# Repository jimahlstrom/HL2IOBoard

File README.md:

# IO Board for the Hermes Lite 2 by N2ADR
**January 6, 2024**

**Please click the left button "-  ----" above for a navigation menu.**

**Register names are now fixed, but there may be additions. Further documentation is coming, stay tuned.
Please provide feedback, especially if you see a problem.**

This project is a 5 by 10 cm printed circuit board and related firmware. The board mounts in the same box as the Hermes Lite 2.
It mounts above the N2ADR filter board if one is installed.
The filter board and the IO board are independent of each other.
The PC running the SDR software sends the transmit frequency to the board.
The microcontroller on the board then uses the board's switches to control an amplifier, switch antenns or transverters, etc.
There are a variety of IO resources available and there will be different microcontroller software for each application.
The IO board is meant to be a general purpose solution to control hardware attached to the HL2.

The IO board could also be connected to the I2C bus on a single board computer to provide station control.

The board has a Pico microcontroller and IO resources including
5 volt gates, low side switches, a fan controller, and a UART. There are two SMA connectors for a separate Rx input and a Pure Signal input.
The board plugs into the [Hermes Lite 2](http://www.hermeslite.com) main board and replaces the 2x20
jumper that connects to the N2ADR filter board.
The board sits directly above the filter board (if any) as shown in the photos below.

To use the board it will be necessary to choose which switches you need and solder wire jumpers from the switches to the DB9 connector.
Then you must write or download firmware for the Pico that will operate the switches based on the transmit frequency.

#### IO board mounted above the filter board

#### Top view of the board

#### Bottom view of the board

## Modification to the HL2 Main Board
The HL2 main board must be modified by adding three extra header pins. In the picture below, look at the normal 20 pin
header at the back edge of the board. Following that, two holes are skipped, and then a 1x3 header is added. This changes the
20 pin header to a 25 pin header with two unused pins. The extra pins provide 3.3 volts, ground and VSUP.
VSUP is the 12 volt HL2 input supply taken after the fuse.
It is convenient to place the 2x20 pin header across the existing pins and the three added pins to provide
alignment when soldering. The IO board has a 2x25 pin header. When installed, this connects the HL2 to the filter board as usual.

For the three-pin header you need the same size as the 1x20 header on the main HL2 board. The pin pitch is 2.54 mm.
On my HL2, the total height is 11.43 mm with 3.05 mm below the PCB. The pins are square and 0.64 mm on a side.
But my HL2 is an old one, so check what size your pins are. The exact height is not too critical.

#### Added three-pin header

## Initial Testing of the IO Board
Please test the IO board when you get it.
First program the Pico with the test program.
Power off the HL2 and connect a USB cable to the IO Board.
Push the button on the Pico and then plug the USB cable into your PC.
The Pico will appear as a flash drive on the PC. Then copy the file n2adr_test/build/main.uf2 to the Pico. The Pico will reboot and the Pico LED will flash slowly.

Now apply power to the HL2. Use an oscilloscope to see the test signals.
  * Look for pulses of 1,2,3,4,5,6,7 milliseconds on J4 pins 1 to 7.
  * Look for 3.0 volts DC on J4 pin 8.
  * Look for 0.5 * supply voltage at J3 pin 1.
  * Look for a 5.0 volt 500 Hz square wave at Sw5.
  * Look for a supply voltage 250 Hz square wave at Sw12.

Connector J6 has MOSFETs that short the pin to ground.
To test, connect a DC voltage of 3.3 to 16 volts to one end of a resister of a few thousand ohms.
Connect the other end to an oscilloscpe, and use this end to probe J6 pins 1 to 7.
You should see the same signal as on J4 but with reverse polarity.

The test program can generate a test pattern for the antenna tuner protocol. Write a "1" to REG_ANTENNA_TUNER. SDR authors can use this to help write code for this feature. 

## Design of the IO Board Hardware
The IO board is a four-layer PCB. Rather large parts are used, with none smaller than 0805 (2012 metric). It is designed to be easy to solder at home. It is only necessary to mount the parts you plan to use.

Please refer to the [schematic](KiCad/HL2IOBoard.pdf).
The IO board has two I2C addresses. Address 0x41 register 0 is a read only register that returns the hardware version number
in bits 3 to 0, and 0xF in bits 7 to 4. So for this hardware version, it returns 0xF1. If other IO boards become available,
they will return different version numbers. This is the hardware version and will be returned even if the firmware is not running.
Reading this register can test whether the filter board is installed.

The Pico microcontroller listens to I2C address 0x1D. This is distinct from the filter board I2C address, and the IO board will
not conflict with or control the filter board. The IO board has these resources controlled by the Pico:

 * Eight 5 volt CMOS outputs and eight low-side switches (mosfets to ground). Both are controlled by the same Pico pin,
so they can be used in any combination, but only up to eight total. They are high speed except for output 8. This has an RC filter and is intended for
optional zero to five volt PWM DC output. The DC output can be programmed to change according to the band in use, and is used to
change bands in external amplifiers. If not needed, output 8 can still be an output, but at slow speed.
 * Five logic inputs that are protected, and work from plus 3.3 to 20 volts.
 * A source of switched 12 volt power.
 * A source of switched 5 volt power.
 * A variable DC voltage from zero to about 12 volts. This is intended to drive a fan.
 * A logic input that reads the state of EXTTR from the HL2.
 * An SMA receive input.
 * Control for a switched high pass filter in the receive input.
 * An SMA Pure Signal input.
 * Pico GPIO 5 is unused.
 * Pico GPIO 26, 27 and 28 are unused. They can be used for 3.3 volt logic or for ADC inputs. The ADC reference is 3.00 volts.
 * Any Pico pins can be used directly at 3.3 volt logic.

These resources can be used for various purposes. The Pico has two UARTs. Output 1 and Input 1 can be used for UART Tx and Rx.
Note that the signal voltages are zero and five volts. This is common for communication between microcontrollers.
But the standard RS232 levels are more like plus and minus eight volts, so a connection to a PC will require an interface IC.

A "low-side switch" is a mosfet to ground. They are commonly used to switch relays. But they can also implement a wired-or bus
such as a one-wire bus or an I2C bus. The Icom AH-4 antenna tuner can be controlled this way. The switches are implemented
in a TBD62381AFWG,EL integrated circuit. This has an absolute maximum rating of 50 volts and 500 ma per channel.

**These low-side switches are NOT protected against inductive loads. Always place a diode across relay coils and any other inductive load.**

There is a 15x18 mm bare copper area for prototyping. There is a 1x5 header J2 and a 1x2 header J12 to plug in a perf board for additional area.

The board has a DB9 connector and the pins are wired to a 1x9 pin header. The outputs go to two 2x4 headers, and the inputs go to a 1x5 header.
Other IO goes to small pads. The headers are not installed. Wire everything up as desired with hookup
wire to the pads and to the DB9 pads. Of course, you can add headers if desired.

### Table of IO Resources

|Software Pin Name |Usage|Connector Reference|
|------------------|-----|-------------------|
|GPIO00_HPF|Control HPF in Rx path||
|GPIO01_Sw12|Switched VSUP (usually 12 volts)|Sw12|
|GPIO02_RF3|Control Pure Signal input||
|GPIO03_INTTR|Control HL2 T/R relay||
|GPIO04_Fan|Zero to 11.5 fan voltage|J3|
|GPIO05_xxx|not connected||
|GPIO06_In5|Protected logic input|J8 pin 5|
|GPIO07_In4|Protected logic input|J8 pin 4|
|GPIO08_Out8|5V logic ; low side switch|J4 pin 8 ; J6 pin 8|
|GPIO09_Out7|5V logic ; low side switch|J4 pin 7 ; J6 pin 7|
|GPIO10_Out5|5V logic ; low side switch|J4 pin 5 ; J6 pin 5|
|GPIO11_Out4|5V logic ; low side switch|J4 pin 4 ; J6 pin 4|
|GPIO12_Sw5|Switched 5 volts|Sw5|
|GPIO13_EXTTR|Logic input EXTTR, High for Rx, low for Tx||
|GPIO14_I2C1_SDA|HL2 I2C bus||
|GPIO15_I2C1_SCL|HL2 I2C bus||
|GPIO16_Out1|5V logic ; low side switch|J4 pin 1 ; J6 pin 1|
|GPIO17_In1|Protected logic input|J8 pin 1|
|GPIO18_In2|Protected logic input|J8 pin 2|
|GPIO19_Out2|5V logic ; low side switch|J4 pin 2 ; J6 pin 2|
|GPIO20_Out3|5V logic ; low side switch|J4 pin 3 ; J6 pin 3|
|GPIO21_In3|Protected logic input|J8 pin 3|
|GPIO22_Out6|5V logic ; low side switch|J4 pin 6 ; J6 pin 6|
|GPIO25_LED|Pico on-board LED||
|GPIO26_ADC0|not connected||
|GPIO27_ADC1|not connected||
|GPIO28_ADC2|not connected||

## IO Board Pico Firmware
### Installing Firmware
Firmwares for the Pico are in subdirectories of HL2IOBoard. Look in the source files to see what they do.

- n2adr_test   Test program to toggle the 5 volt outputs.
- n2adr_basic  Very basic example.
- n2adr_lib    Library of useful subroutines used in the above.
- n1adj_hr50   Control the [Hardrock-50](https://hobbypcb.com/products/hardrock-50-hf-power-amp-kit) amplifier.

To create your own firmware, install the Pico SDK and create a directory for your code.
You may want to clone my github project to get you started.
Export the location of your SDK: export PICO_SDK_PATH=/home/jim/etc/pico-sdk.
Copy the file pico-sdk/external/pico_sdk_import.cmake to your directory.
Copy my CMakeLists.txt and main.c to your directory and edit them as desired.
Make a "build" subdirectory.
Change directories to the build directory and enter "cmake .." and "make".
See the Pico documentation for more detail.
Be careful with i2c_slave_handler(), as it is an interrupt service routine. Return quickly and do not put printf's here! Just set a flag and look for it in the loop at the end of main().

To install the firmware, power off the HL2 and connect a USB cable to the IO Board.
Push the button on the Pico and then plug the USB cable into your PC.
The Pico will appear as a flash drive on the PC. Then copy the file build/main.uf2 to the Pico. 

There is an LED on the Pico. When the firmware is running, it flashes slowly. When the Pico receives I2C traffic directed to its address, it flashes faster.

### Firmware Design

The Pico listens to I2C address 0x1D and you can read and write to registers at this I2C address. Writes always send a one-byte address and one byte of data. Since the address is one byte, the data item is stored in a 256 byte array named "Registers".
All registers are initialized to zero at power on and after a software reset.
You can write to any register, not just the ones in the table below.
So a write to register REG_ANTENNA_TUNER (equal to 7) looks like this:

Registers[REG_ANTENNA_TUNER] = datum;

Reads always send a one byte address and return four bytes of data.
A read from register REG_ANTENNA_TUNER returns Registers[REG_ANTENNA_TUNER] and the next three registers.

There are some exceptions to this general pattern and all are noted below.

The Pico is an I2C slave device, so reads and writes result in a call to the interrupt service routine
in i2c_slave_handler.c. This routine must return fast to avoid hanging the bus. So a typical program would
not alter i2c_slave_handler.c. It would have a polling loop in main.c to check for changes in any registers
it cares about and would perform needed actions there.

#### Frequency Codes

The files n2adr_lib/frequency_code.c and frequency_code.py contain functions to convert a frequency in hertz to a one-byte code,
and to convert a code back to a frequency. The code is a useful one-byte approximation of the frequency
which is sufficient to recognize the band and to select antennas.
The codes are monotonic in frequency. The special code zero means the frequency was not entered and is unspecified.
A table of all the codes is at [frequencycodes.html](http://james.ahlstrom.name/frequencycodes.html).
Run the Python file "python frequency_code.py" to print your own table of codes.

#### Band Codes

A band code is a single frequency code for each band.
The band code is chosen to be as close to the band frequency as possible. All other frequency codes are assigned to the closest band code.
A table of band codes is in hl2ioboard.h.
You can use the band code to select antennas, or you can use the frequency code directly.

The band code is convenient because some bands have multiple frequency codes. And since all frequency codes resolve to the
closest band code, there are no gaps in coverage. If you tune outside the band, the closest band antenna is chosen.

#### Global Variables

These global variables are set in i2c_slave_handler() when data is received:

  * extern uint64_t new_tx_freq;
  * extern uint8_t new_tx_fcode;

The Tx frequency and Tx frequency code are set when the Tx frequency changes.

  * extern bool rx_freq_changed;
  * extern uint8_t rx_freq_high;
  * extern uint8_t rx_freq_low;

These are set when any of the twelve Rx frequencies change. If all Rx frequencies are zero, rx_freq_high and low are both zero.

  * extern uint8_t Registers[256];

This is the array of all register data.

  * extern uint8_t firmware_version_major;
  * extern uint8_t firmware_version_minor;

You must set the version in your main routine so it can be returned to software.

#### Library Functions

The directory n2adr_lib contains utility functions to make writing Pico software easier.

  * void configure_led_flasher(void)

Call this once near the start of your Pico program. It controls flashing the Pico LED.

  * void configure_pins(bool use_uart1, bool use_pwm4a)

This sets the configuration of the Pico GPIO pins, and you must call this once near the start of your program.
If use_uart1, J8 pin 1 and J4 pin 1 are UART pins; otherwise they are regular logic.
If use_pwm4a, J4 pin 8 is used for a variable 0 to 5 volt band voltage; otherwise it is regular logic.

  * uint8_t hertz2fcode(uint64_t hertz)
  * uint64_t fcode2hertz(uint8_t code)

These functions convert between a 5-byte frequency and a 1-byte frequency code. They are in frequencycode.c.
The file frequencycode.py is the same code in Python, and it is not used here. It is included for convenience.

  * uint8_t fcode2band(uint8_t fcode)

This converts a frequency code to a band code. A band code is a single frequency code for each band. See below.

  * void ft817_band_volts(uint8_t band_code)
  * void xiegu_band_volts(uint8_t band_code)

These are used to generate a zero to five volt band voltage on J4 pin 8.

  * i2c_slave_handler.c

This contains the I2C interrupt handler that is called for I2C reads and writes. Since it must return quickly,
it mostly sets registers and global variables that you can test in a loop in your Pico program.
When it receives the Tx frequency, it sets new_tx_freq to the frequency and new_tx_fcode to the corresponding frequency code.
It also uses firmware_version_major and firmware_version_minor, and you must set these in your Pico program.

  * icom_ah4.c

This contains code to control the Icom AH4 antenna tuner. It is untested.

#### Table of I2C Registers

When you write code, please use the register names shown. The names are in i2c_registers.h.

|Register|Name|Description|
|--------|----|-----------|
|0|REG_TX_FREQ_BYTE4|Most significant byte of the 5-byte Tx frequency in Hertz|
|1|REG_TX_FREQ_BYTE3|Next Tx frequency byte|
|2|REG_TX_FREQ_BYTE2|Next Tx frequency byte|
|3|REG_TX_FREQ_BYTE1|Next Tx frequency byte|
|4|REG_TX_FREQ_BYTE0|The least significant byte of the Tx frequency.|

The transmit frequency is a five-byte integer number in hertz. You can send BYTE1 to BYTE4 in any order.
When BYTE0 is sent, the Pico will update the global 64-bit integer new_tx_freq and the 8-bit frequency code new_tx_fcode.
This happens in an interrupt service routine in n2adr_lib/i2c_slave_handler.c.
Use a polling routine in your main.c to look for changes. See the example in n2adr_basic.
If a transverter is in use, the Tx frequency includes the transverter offset.

|Register|Name|Description|
|--------|----|-----------|
|5|REG_CONTROL|Write 1 to reset all the registers to zero.|
|6|REG_INPUT_PINS|Read only. The input pin bits: In5, In4, In3, In2, In1, Exttr|
|7|REG_ANTENNA_TUNER|Control an antenna tuner|

A write to register REG_ANTENNA_TUNER is a command to the tuner. I am modeling this on the Icom AH-4 but I want it to work in general.
See the code in n2adr_lib/icom_ah4.c.
A write of 1 starts a tune request.
A write of 2 is a bypass command. Other tuners may have more commands. The Pico will talk to the ATU and change the register to higher numbers to indicate progress.
The PC must read this register while tuning progresses. If the register reads as 0xEE the PC must send RF to the ATU, and stop RF when 0xEE stops.
A final value of zero indicates a successful tune. Values of 0xF0 and higher indicate that tuning failed.
Note that the IO board can not initiate RF and so the need for 0xEE.
SDR software is not required to implement this command. In the future there may be an external program to do this.

|Register|Name|Description|
|--------|----|-----------|
|8|REG_FAULT|Read only. Zero for no fault. The meaning of non-zero codes is not currently defined.|
|9|REG_FIRMWARE_MAJOR|Read only. Firmware major version|
|10|REG_FIRMWARE_MINOR|Read only. Firmware minor version|
|11|REG_RF_INPUTS|The receive input usage, 0, 1 or 2.|

REG_RF_INPUTS determines how the SMA receive input J9 and the Pure Signal input J10 are used.
Mode 0 means that J9 is not used, and the usual HL2 input is the receive input.
In mode 0 the Pure Signal input J10 is mixed with the receive signal.
For modes 1 and 2, J9 is used instead of the usual HL2 receive input.
Mode 1 means that J9 is used for the receive signal and the Pure Signal input is not available.
Mode 2 means that for receive, J9 is used for the receive signal;
and that for transmit, the Pure Signal input is passed to the HL2 instead of a receive signal.

|Register|Name|Description|
|--------|----|-----------|
|12|REG_FAN_SPEED|The fan voltage as a number from 0 to 255|
|13|REG_FCODE_RX1|The frequency code for the first receiver RX1|
|14-24|REG_FCODE_RX2 to RX12|The frequency code for receiver RX2 to RX12|

The HL2 can have from one to twelve independent receivers. SDR software can use this feature
to scan multiple bands for digital or CW signals. Choosing an antenna requires knowing all the Rx frequencies.
The Rx frequencies are sent as a one-byte frequency code to registers 13 to 24 with names REG_FCODE_RX1 to RX12.
The HL2 always has RX1, but if it is unspecified (zero) it is the same as the Tx frequency.
If any Rx frequency is changed, the global boolean rx_freq_changed is set to true.
If a transverter is in use, the Rx frequency includes the transverter offset.

|Register|Name|Description|
|--------|----|-----------|
|25|REG_ADC0_MSB|The most significant byte of ADC0|
|26|REG_ADC0_LSB|The least significant byte of ADC0|
|27|REG_ADC1_MSB|The most significant byte of ADC1|
|28|REG_ADC1_LSB|The least significant byte of ADC1|
|29|REG_ADC2_MSB|The most significant byte of ADC2|
|30|REG_ADC2_LSB|The least significant byte of ADC2|

The Pico has one 12-bit ADC that can read from ADC0, ADC1 and ADC2 on pins GPIO26, GPIO27 and GPIO28.
Always read the most significant byte first because that triggers the conversion.
A read from ADC0 returns the value of ADC0 and ADC1 in the four byte response.
A read from ADC1 returns the value of ADC1 and ADC2.
Reading the two values in quick succession can be used to calculate SWR from forward and reverse power.

|Register|Name|Description|
|--------|----|-----------|
|31|REG_ANTENNA|Choose among multiple antennas|

Normally, the antenna choice is calculated by the Pico based on the Tx and Rx frequencies.
But there may be multiple antennas available for a single band.
The high four bits of REG_ANTENNA is the Tx antenna, and the low four bits is the Rx antenna for the current band.
A zero means the first (default) antenna.

|Register|Name|Description|
|--------|----|-----------|
|32|REG_OP_MODE|Set the operating Mode|

||Mode|Value|Mode|Value|Mode|Value|Mode|Value|
|---|---|---|---|---|---|---|---|---|
||LSB|0|USB|1|DSB|2|CWL|3|
||CWU|4|FM|5|AM|6|DIGU|7|
||SPEC|8|DIGL|9|SAM|10|DRM|11|
||AM_LSB|12|AM_USB|13|

Operating mode values are based on Thetis internal definitions.
Note that value zero does not mean "unspecified".

|Register|Name|Description|
|--------|----|-----------|
|167|REG_STATUS|Read or write to Sw5 and Sw12. Read the In1 configuration.|
|168|REG_IN_PINS|Same as REG_INPUT_PINS plus Out1 and Out8 configuration.|
|169|REG_OUT_PINS|Read or write to GPIO Out8 to Out1 directly.|
|170|GPIO_DIRECT_BASE|Map this register to GPIO 0|
|171-198||GPIO 1 to 28|

A read or write to registers GPIO_DIRECT_BASE to GPIO_DIRECT_BASE + 28 reads or writes to the Pico GPIO pins 0 to 28.
This supports using Steve's hermeslite.py or similar to control the Pico registers directly.
A user could write a program to switch antennas without adding C code to the Pico.
Since the SDR program writes Tx and Rx frequencies to the Pico, a third party program could read them back to select the antenna.
For C programmers, it would still be easier to write the code into the Pico.

The other registers add further support. Bits are numbered from 7 to zero and the most significant bit is 7.

  * REG_STATUS

Bit 0 is Sw5, bit 1 is Sw12, bit 2 is 1 if In1 is configured as a UART.

  * REG_IN_PINS

This is read-only. It is the same as REG_INPUT_PINS, and adds two bits. Bit 6 is 1 if Out1 is configured as UART.
Bit 7 is 1 if Out8 is configured as band volts.

  * REG_OUT_PINS

This reads and writes Out1 to Out8 directly. Bit 0 is Out1 and bit 7 is Out8.

|Register|Name|Description|
|--------|----|-----------|
|200-255||Reserved for SDR authors. If you use them, please document them.|

## Modifications to SDR PC Software

The IO board connects to the I2C interface in the Hermes Lite 2.
The [HL2 protocol](https://github.com/softerhardware/Hermes-Lite2/wiki/Protocol)
provides a way to send and receive I2C messages from host SDR software to the IO board to control its operation.
Quisk uses the ACK bit with I2C commands. As described in the protocol, these commands should
be sent at intervals so they don't disrupt normal protocol commands.

Since the PC can read and write the I2C bus to communicate with the IO board, it would be possible for SDR software
authors (Quisk, Spark, Power SDR, etc.) to write extensive logic to control IO. This is NOT the desired result. Instead
users should write new Pico firmware to provide the services they require. It is easy to write firmware for the Pico.
Ideally, an owner of a given power amp, for example HR50, would write a custom firmware and provide a wiring diagram for that amp.

**Do NOT ask authors to modify SDR software! Write new firmware instead!**

### Reset

The IO board registers are static and may have old data.
When your SDR program starts, write 1 to REG_CONTROL to set all registers back to zero.

### Transmit Frequency

The only required SDR modification is sending the transmit frequency.
SDR software must send the transmit frequency to provide band information to power amps, transverters and loop antennas.
You can wait for the band to change, and then just send a frequency in the band. For example, if the
user presses the 40 meter button, send 7.0 MHz. This is enough to determine the band, but not enough to tune a loop antenna.
You can send the exact Tx frequency, but since the user is probably doing a lot of tuning, it is best to limit the I2C
traffic. Quisk sends the Tx frequency at a maximum rate of once every 0.5 seconds, and only if it changes. The frequency
data in registers BYTE1 to BYTE4 are static, and are only used when register BYTE0 is written. So you don't need to re-send them unless
they change.

### Receive Frequencies

You may need to send the twelve receive frequencies if your SDR software supports multiple receivers.
The Pico will use this to select a receive antenna, probably by finding the highest frequency and
setting low pass filters to that band. If all Rx frequencies are zero, the Rx band is the same as Tx.

### RF Receive Input

The mode control REG_RF_INPUTS is 0, 1 or 2, and is a user setting. There needs to be an option to set this.

### Fan Control

The fan speed control can be an internal calculation based on temperature, as is currently the case for the fan control
in the HL2 gateware. I don't see the need for a user option for this. Quisk does not implement the fan.

## IO Board Control Software

The software directory contains the Python program n2adr_ioboard.pyw which can be used to control the IO board.
It uses Steve's hermeslite.py software, and a copy is included. To use it, copy the two files to a convenient directory.
You will need to install the netifaces package as follows:

python -m pip install netifaces

Then run the program:

python n2adr_ioboard.pyw

#### Control Program

#### Reduced to a Tool Bar

The program will report the IO board status. You can change the status from the program, and this
may reduce the need to modify SDR programs. It provides a way to control the IO board from Python
rather that write code for the Pico.

Normally the program will search for the HL2. If you need to select one of several HL2's or if searching doesn't work,
enter the IP address and press Enter.

Some fields just report status. Click on the fan voltage or band voltage to change the values.
Click on the GPIO boxes to change the values.
The Macro buttons copy their values to the GPIO row all at once.

The N2ADR control program is not "finished" (does any program ever get finished?) and I invite
a discussion about what it should do.

**End of Documentation**

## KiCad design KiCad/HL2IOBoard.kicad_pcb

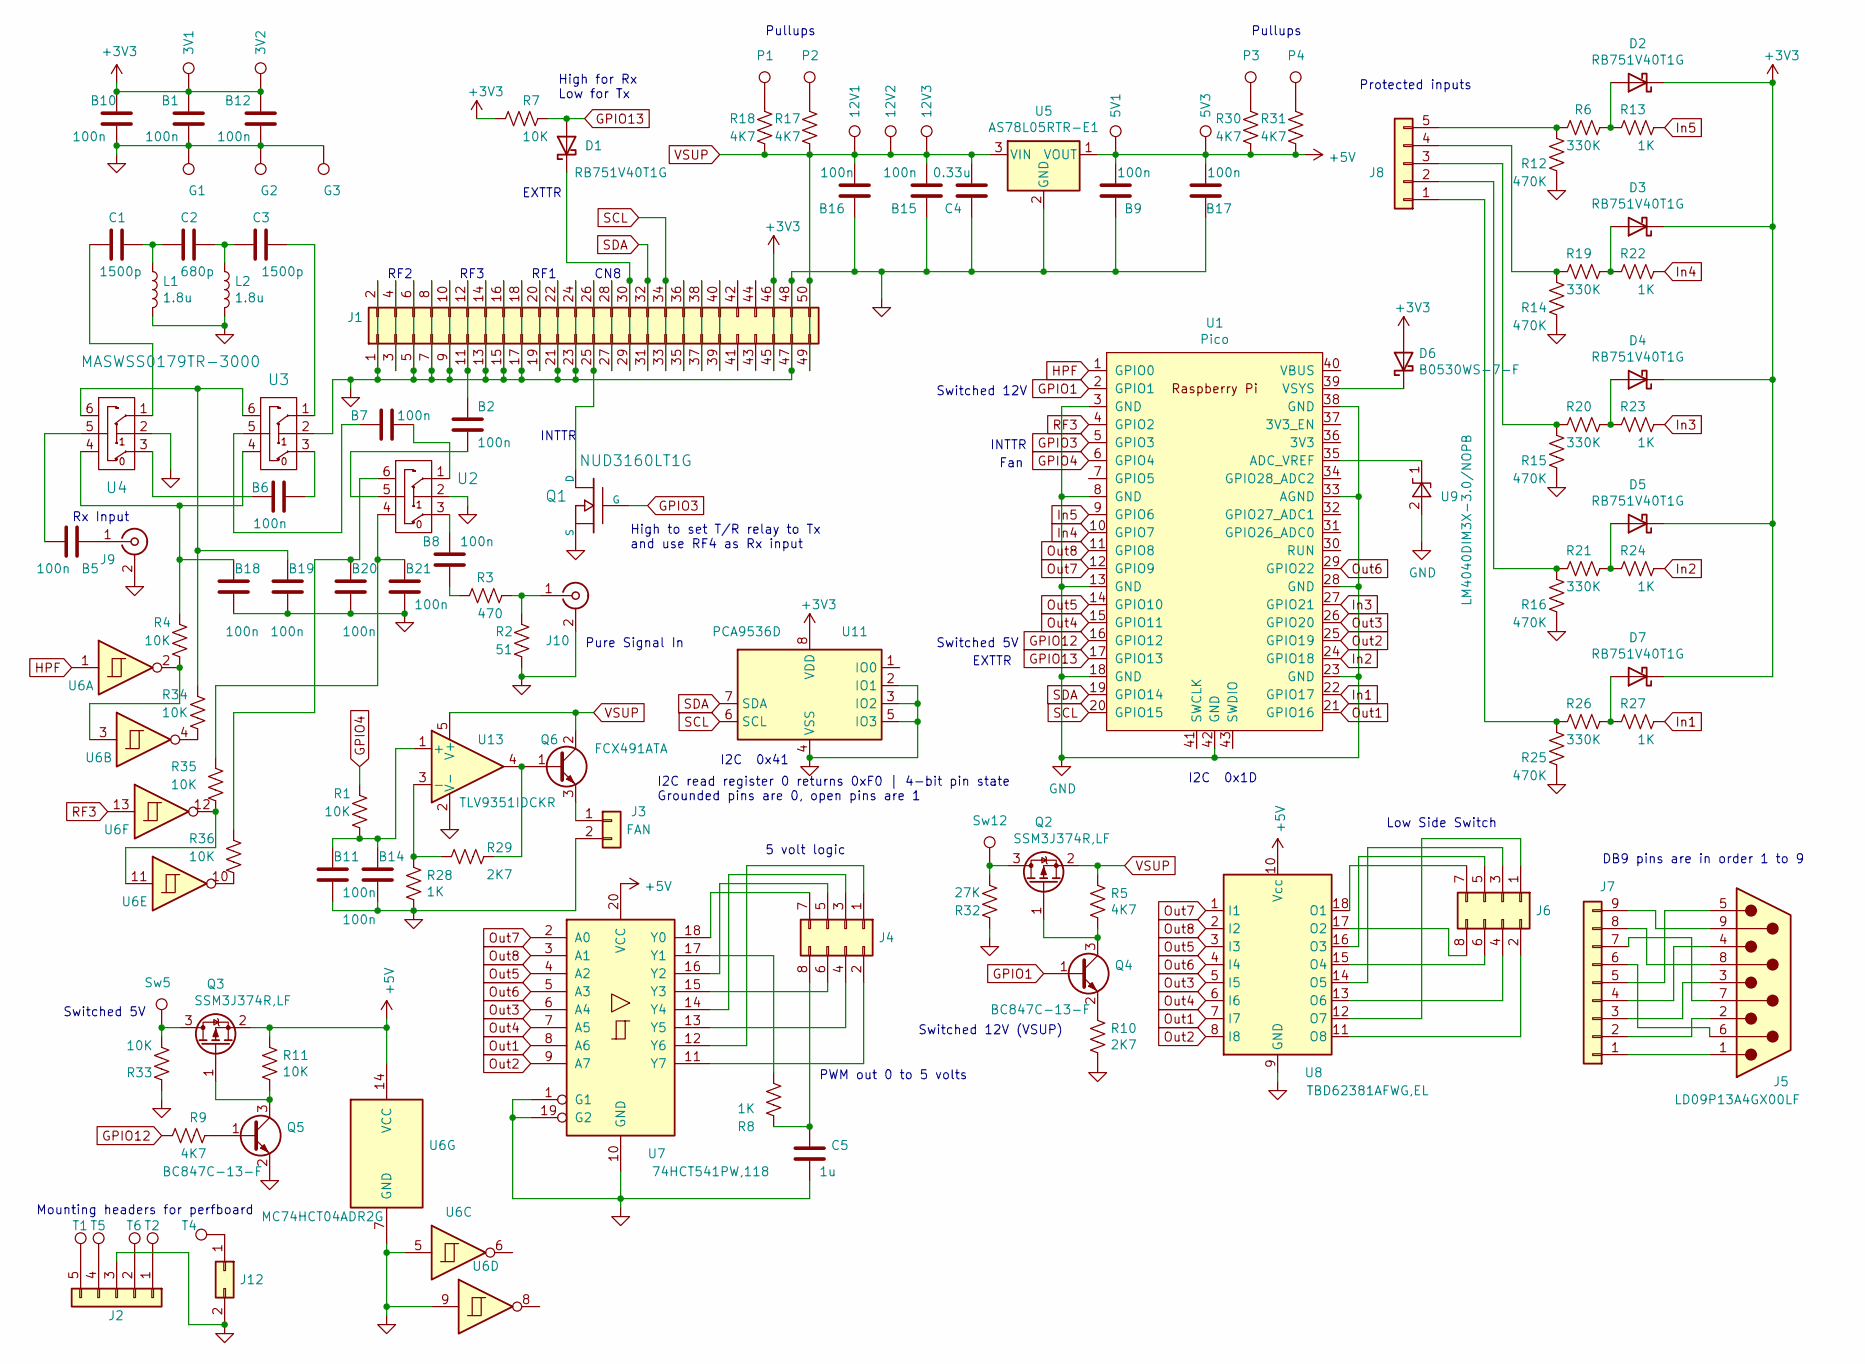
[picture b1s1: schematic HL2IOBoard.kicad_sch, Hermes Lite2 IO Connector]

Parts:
3V1, 3V2, 5V1, 5V3, 12V1, 12V2, 12V3: TestPoint; TestPoint_THTPad_D1.5mm_Drill0.7mm
B1, B2, B5, B6, B7, B8, B9, B10, B11, B12, B14, B15, B16, B17, B18, B19, B20, B21: 100n; C_0805_2012Metric_Pad1.18x1.45mm_HandSolder
C1, C3: 1500p; C_0805_2012Metric_Pad1.18x1.45mm_HandSolder
C2: 680p; C_0805_2012Metric_Pad1.18x1.45mm_HandSolder
C4: 0.33u; C_0805_2012Metric_Pad1.18x1.45mm_HandSolder
C5: 1u; C_0805_2012Metric_Pad1.18x1.45mm_HandSolder
D1, D2, D3, D4, D5, D7: RB751V40T1G; D_SOD-323_HandSoldering
D6: B0530WS-7-F; D_SOD-323_HandSoldering
G1, G2, G3: TestPoint; TestPoint_THTPad_D1.5mm_Drill0.7mm
J1: Conn_02x25_Odd_Even; PinHeader_2x25_P2.54mm_Vertical
J2, J8: Conn_01x05; PinHeader_1x05_P2.54mm_Vertical
J3: FAN; PinHeader_1x02_P2.54mm_Vertical
J4, J6: Conn_02x04_Odd_Even; PinHeader_2x04_P2.54mm_Vertical
J5: LD09P13A4GX00LF; DSUB-9_Male_Horizontal_P2.77x2.84mm_EdgePinOffset9.90mm_Hou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
J7: Conn_01x09; PinHeader_1x09_P2.54mm_Vertical
J9, J10: 142-0701-851; BNCEDGE
J12: Conn_02x01; PinHeader_1x02_P2.54mm_Vertical
L1, L2: 1.8u; L_0805_2012Metric_Pad1.15x1.40mm_HandSolder
P1, P2, P3, P4: TestPoint; TestPoint_THTPad_D1.5mm_Drill0.7mm
Q1: NUD3160LT1G; SOT23_3
Q2, Q3: SSM3J374R,LF; SOT-23
Q4, Q5: BC847C-13-F; SOT-23
Q6: FCX491ATA; SOT-89-3
R1, R4, R7, R11, R33, R34, R35, R36: 10K; R_0805_2012Metric_Pad1.20x1.40mm_HandSolder
R2: 51; R_0805_2012Metric_Pad1.20x1.40mm_HandSolder
R3: 470; R_0805_2012Metric_Pad1.20x1.40mm_HandSolder
R5, R9, R17, R18, R30, R31: 4K7; R_0805_2012Metric_Pad1.20x1.40mm_HandSolder
R6, R19, R20, R21, R26: 330K; R_0805_2012Metric_Pad1.20x1.40mm_HandSolder
R8, R13, R22, R23, R24, R27, R28: 1K; R_0805_2012Metric_Pad1.20x1.40mm_HandSolder
R10, R29: 2K7; R_0805_2012Metric_Pad1.20x1.40mm_HandSolder
R12, R14, R15, R16, R25: 470K; R_0805_2012Metric_Pad1.20x1.40mm_HandSolder
R32: 27K; R_0805_2012Metric_Pad1.20x1.40mm_HandSolder
Sw5, Sw12: TestPoint; TestPoint_THTPad_D1.5mm_Drill0.7mm
T1, T2, T4, T5, T6: TestPoint; TestPoint_THTPad_D1.5mm_Drill0.7mm
U1: Pico; RPi_Pico_SMD_TH
U2, U3, U4: MASWSS0179TR-3000; SOT-23-6_Handsoldering
U5: AS78L05RTR-E1; SOT-89-3_Handsoldering
U6: MC74HCT04ADR2G; SO-14_3.9x8.65mm_P1.27mm
U7: 74HCT541PW,118; TSSOP-20_4.4x6.5mm_P0.65mm
U8: TBD62381AFWG,EL; SOIC-18W_7.5x11.6mm_P1.27mm
U9: LM4040DIM3X-3.0/NOPB; SOT-23
U11: PCA9536D; SOIC-8_3.9x4.9mm_P1.27mm
U13: TLV9351IDCKR; SOT-353_SC-70-5_Handsoldering

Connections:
+3V3: 3V1.1, 3V2.1, B1.2, B10.1, B12.2, D2.1 (K), D3.1 (K), D4.1 (K), D5.1 (K), D6.2 (A), D7.1 (K), J1.45, J1.46, R7.2, U11.8 (VDD)
+5V: 5V1.1, 5V3.1, B9.2, B17.2, Q3.2 (S), R11.1, R30.2, R31.2, U5.1 (VOUT), U6.14 (VCC), U7.20 (VCC), U8.10 (Vcc)
GND: B1.1, B9.1, B10.2, B11.2, B12.1, B14.2, B15.1, B16.1, B17.1, B18.2, B19.2, B20.2, B21.2, C4.1, C5.2, G1.1, G2.1, G3.1, J1.1, J1.2, J1.5, J1.6, J1.7, J1.8, J1.9, J1.10, J1.13, J1.14, J1.15, J1.16, J1.17, J1.18, J1.21, J1.22, J1.23, J1.24, J1.47, J1.48, J2.3, J3.2, J9.2 (Ext), J10.2 (Ext), J12.2, L1.2, L2.2, Q1.2 (S), Q5.2 (E), R2.2, R10.2, R12.1, R14.1, R15.1, R16.1, R25.1, R28.2, R32.2, R33.2, U1.3 (GND), U1.8 (GND), U1.13 (GND), U1.18 (GND), U1.23 (GND), U1.28 (GND), U1.33 (AGND), U1.38 (GND), U1.42 (GND), U2.2, U3.2, U4.2, U5.2 (GND), U6.5, U6.7 (GND), U6.9, U7.1 (G1), U7.10 (GND), U7.19 (G2), U8.9 (GND), U9.2 (A), U11.2 (IO1), U11.3 (IO2), U11.4 (VSS), U11.5 (IO3), U13.2 (V-)
GPIO1: Q4.1 (B), U1.2 (GPIO1)
GPIO3: Q1.1 (G), U1.5 (GPIO3)
GPIO4: R1.1, U1.6 (GPIO4)
GPIO12: R9.2, U1.16 (GPIO12)
GPIO13: D1.2 (A), R7.1, U1.17 (GPIO13)
HPF: U1.1 (GPIO0), U6.1
In1: R27.2, U1.22 (GPIO17)
In2: R24.2, U1.24 (GPIO18)
In3: R23.2, U1.27 (GPIO21)
In4: R22.2, U1.10 (GPIO7)
In5: R13.2, U1.9 (GPIO6)
unnamed: B2.1, J1.11, J1.12
unnamed: B2.2, U2.5
unnamed: B5.1, J9.1 (In)
unnamed: B5.2, U4.5
unnamed: B6.1, U4.3
unnamed: B6.2, U3.3
unnamed: B7.1, U3.5
unnamed: B7.2, U2.1
unnamed: B8.1, R3.1
unnamed: B8.2, U2.3
unnamed: B11.1, B14.1, R1.2, U13.1 (+)
unnamed: B18.1, R4.1, U3.4, U4.4
unnamed: B19.1, R34.2, U3.6, U4.6
unnamed: B20.1, R36.2, U2.6
unnamed: B21.1, R35.2, U2.4
unnamed: C1.1, C2.2, L1.1
unnamed: C1.2, U4.1
unnamed: C2.1, C3.2, L2.1
unnamed: C3.1, U3.1
unnamed: C5.1, J4.8, R8.1
unnamed: D1.1 (K), J1.29, J1.30
unnamed: D2.2 (A), R6.2, R13.1
unnamed: D3.2 (A), R19.2, R22.1
unnamed: D4.2 (A), R20.2, R23.1
unnamed: D5.2 (A), R21.2, R24.1
unnamed: D6.1 (K), U1.39 (VSYS)
unnamed: D7.2 (A), R26.2, R27.1
unnamed: J1.3, J1.4
unnamed: J1.19, J1.20
unnamed: J1.25, J1.26, Q1.3 (D)
unnamed: J1.27, J1.28
unnamed: J1.35, J1.36
unnamed: J1.37, J1.38
unnamed: J1.39, J1.40
unnamed: J2.1, T2.1
unnamed: J2.2, T6.1
unnamed: J2.4, T5.1
unnamed: J2.5, T1.1
unnamed: J3.1, Q6.3 (E)
unnamed: J4.1, U7.12 (Y6)
unnamed: J4.2, U7.11 (Y7)
unnamed: J4.3, U7.14 (Y4)
unnamed: J4.4, U7.13 (Y5)
unnamed: J4.5, U7.16 (Y2)
unnamed: J4.6, U7.15 (Y3)
unnamed: J4.7, U7.18 (Y0)
unnamed: J5.1, J7.1
unnamed: J5.2, J7.2
unnamed: J5.3, J7.3
unnamed: J5.4, J7.4
unnamed: J5.5, J7.5
unnamed: J5.6, J7.6
unnamed: J5.7, J7.7
unnamed: J5.8, J7.8
unnamed: J5.9, J7.9
unnamed: J6.1, U8.12 (O7)
unnamed: J6.2, U8.11 (O8)
unnamed: J6.3, U8.14 (O5)
unnamed: J6.4, U8.13 (O6)
unnamed: J6.5, U8.16 (O3)
unnamed: J6.6, U8.15 (O4)
unnamed: J6.7, U8.18 (O1)
unnamed: J6.8, U8.17 (O2)
unnamed: J8.1, R25.2, R26.1
unnamed: J8.2, R16.2, R21.1
unnamed: J8.3, R15.2, R20.1
unnamed: J8.4, R14.2, R19.1
unnamed: J8.5, R6.1, R12.2
unnamed: J10.1 (In), R2.1, R3.2
unnamed: J12.1, T4.1
unnamed: P1.1, R18.1
unnamed: P2.1, R17.1
unnamed: P3.1, R30.1
unnamed: P4.1, R31.1
unnamed: Q2.1 (G), Q4.3 (C), R5.2
unnamed: Q2.3 (D), R32.1, Sw12.1
unnamed: Q3.1 (G), Q5.3 (C), R11.2
unnamed: Q3.3 (D), R33.1, Sw5.1
unnamed: Q4.2 (E), R10.1
unnamed: Q5.1 (B), R9.1
unnamed: Q6.1 (B), R29.1, U13.4
unnamed: R4.2, U6.2, U6.3
unnamed: R8.2, U7.17 (Y1)
unnamed: R28.1, R29.2, U13.3 (-)
unnamed: R34.1, U6.4
unnamed: R35.1, U6.11, U6.12
unnamed: R36.1, U6.10
unnamed: U1.35 (ADC_VREF), U9.1 (K)
Out1: U1.21 (GPIO16), U7.8 (A6), U8.7 (I7)
Out2: U1.25 (GPIO19), U7.9 (A7), U8.8 (I8)
Out3: U1.26 (GPIO20), U7.6 (A4), U8.5 (I5)
Out4: U1.15 (GPIO11), U7.7 (A5), U8.6 (I6)
Out5: U1.14 (GPIO10), U7.4 (A2), U8.3 (I3)
Out6: U1.29 (GPIO22), U7.5 (A3), U8.4 (I4)
Out7: U1.12 (GPIO9), U7.2 (A0), U8.1 (I1)
Out8: U1.11 (GPIO8), U7.3 (A1), U8.2 (I2)
RF3: U1.4 (GPIO2), U6.13
SCL: J1.33, J1.34, U1.20 (GPIO15), U11.6 (SCL)
SDA: J1.31, J1.32, U1.19 (GPIO14), U11.7 (SDA)
VSUP: 12V1.1, 12V2.1, 12V3.1, B15.2, B16.2, C4.2, J1.49, J1.50, Q2.2 (S), Q6.2 (C), R5.1, R17.2, R18.2, U5.3 (VIN), U13.5 (V+)

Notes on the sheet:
CN8
Rx Input
Protected inputs
Pure Signal In
PWM out 0 to 5 volts
EXTTR
RF1
INTTR
RF3
High to set T/R relay to Tx and use RF4 as Rx input
Mounting headers for perfboard
Fan
Pullups
I2C 0x41
5 volt logic
Switched 12V
I2C 0x1D
I2C read register 0 returns 0xF0 | 4-bit pin state Grounded pins are 0, open pins are 1
Switched 5V
Switched 12V (VSUP)
Low Side Switch
DB9 pins are in order 1 to 9
RF2
High for Rx Low for Tx

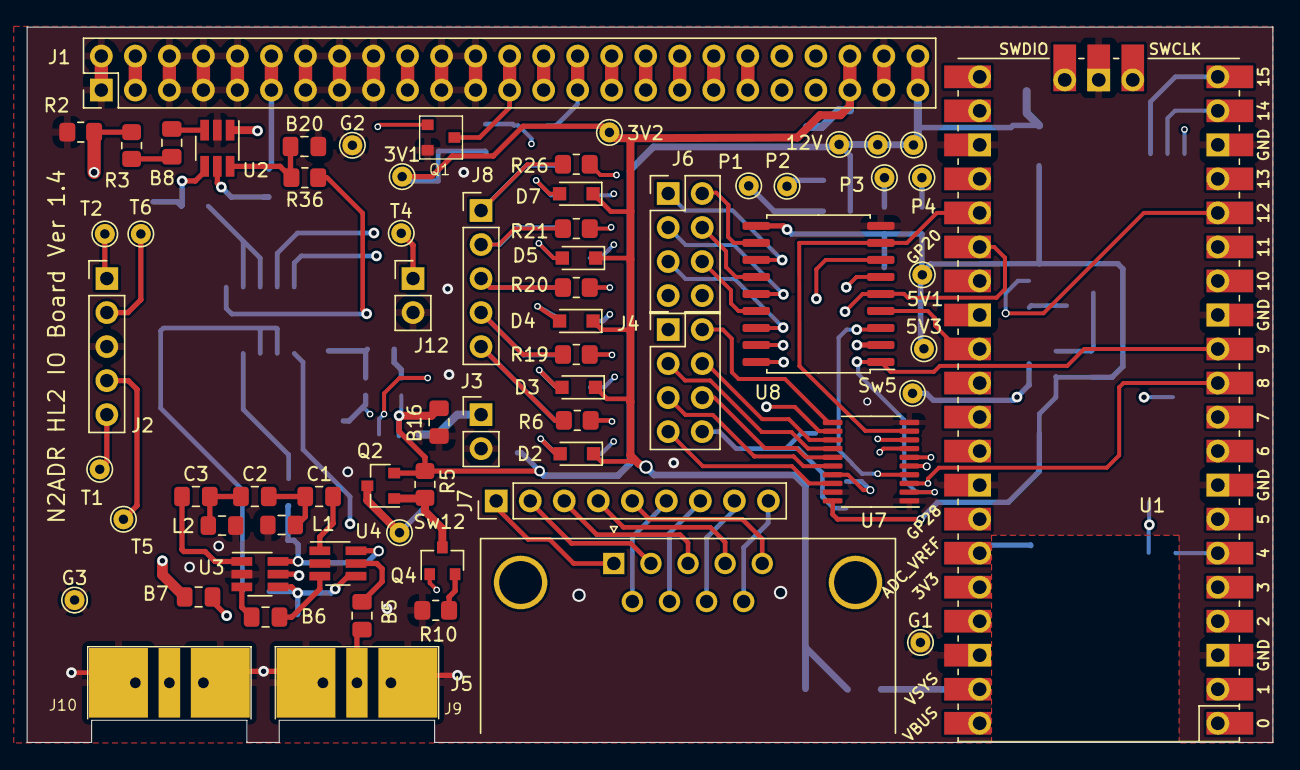
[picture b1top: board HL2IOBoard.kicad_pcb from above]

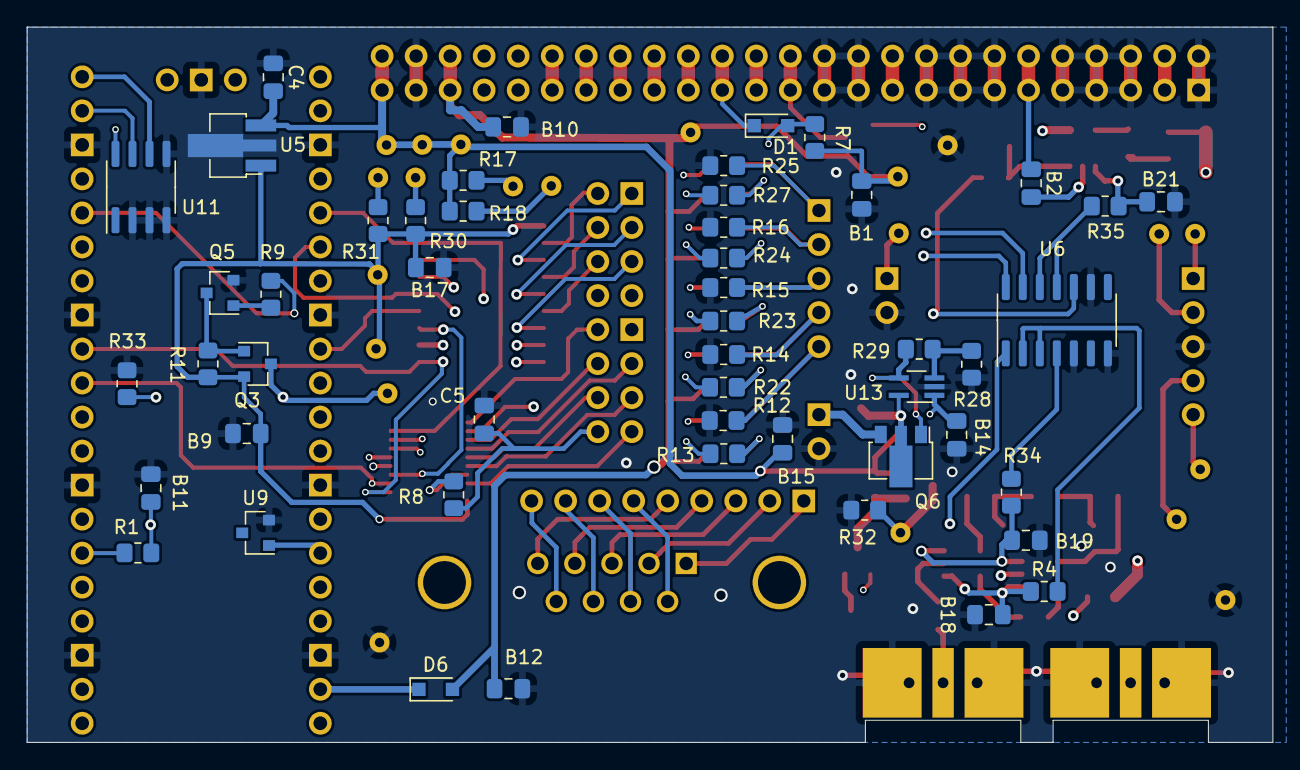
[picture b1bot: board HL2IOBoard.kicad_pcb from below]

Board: 4 copper layers, 93.0 x 53.4 mm, 117 parts (50 on the bottom side), 114 nets.

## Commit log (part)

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2022-04-18 First commit. Add README.md.
2022-04-18 Add pictures.
2022-04-18 Add MIT.txt license file.
2022-04-23 Removed the register for band index and replaced it with Tx frequency.
2022-04-28 Changed the register numbers for write I2C.
2022-04-28 Corrected date of change.
2022-04-28 Added changed schematic.
2022-05-07 Added text to README.md.
2022-05-14 Added the KiCad and source files.
2022-05-15 Add gerber files to KiCad/gerber.
2023-03-14 Patch to main.c by G4BRK, substitute for PCA9536D
2023-03-28 Change the PCB to version 1.4 (Rev E) to replace the unavailable SSOP part with the SOIC TBD62381AFWG,EL.
2023-03-30 Change gerber file format to that requested by Makerfabs.
2023-04-04 Add new source directories n2adr_*. Small mods to schematic and BOM.
2023-04-11 Minor changes to C code.
2023-04-16 Minor software changes.
2023-05-13 Update README.md
    Add board test procedure.
2023-05-17 Updated pictures to board version 1.4.
2023-06-22 Update README.md. Add a table of I2C registers.
2023-06-26 Update README.md for read registers and antenna tuner.
2023-06-26 An I2C read now reads any register. Add code for an Icom AH-4 antenna tuner.
2023-07-12 Change Tx frequency register names
2023-07-13 Change the antenna tuner register to 7.
2023-07-13 Add the fault register.
2023-07-13 Add file i2c_registers.h.
2023-07-13 Move register names to i2c_registers.h.
2023-07-13 Add register, renumber antenna tuner register.
2023-07-25 Change protocol register numbers.
2023-08-10 Add functions for the one-byte frequency code.
2023-08-12 Use consistent names "fcode" for frequency code functions and variables.
2023-08-12 Change old band codes to new band codes.
2023-08-12 Add documentation to README.md.
2023-08-20 Add missing file fcode2bcode.c.
2023-08-20 Add Rx frequency registers and ADC registers.
2023-08-29 Add band volts for Xiegu. Add documentation.
2023-08-30 Add direct GPIO access. Add Xiegu band volts.
2023-09-09 Add more registers and document them.
2023-09-12 Add the IO board control program.
2023-09-15 Change to PCB.
2023-09-18 Control HPF with the Rx frequency, not Tx frequency.
2023-09-19 Change n2adr_ioboard.pyw to version 1.1.
2023-09-19 Add files for the end plates.
2023-10-18 Add a description of the 3-pin addition to HL2 main board.
2023-11-02 Initial version of IO Board firmware to support the Hardrock-50 amplifier.
2023-12-02 Working implementation of automatic tuning
2023-12-02 Always call gpio_disable_pulls(GPIO17_In1)
2023-12-04 Optionally read SWR from HL2 and use that to setermine when tuning is done
2023-12-04 Remove gpio_disable_pulls() call, since configure_pins() now does it
2023-12-08 Add a test for the antenna tuner protocol.
2023-12-08 Document n2adr_test antenna tuner protocol.
2024-01-06 Addition of Register 32 REG_OP_MODE for operating mode
2024-01-06 Fixed Indentation i2c_registers.h
2024-02-09 Add directory ks7roh_hr50+.
2024-02-11 Change 2x25 connector J1 from 13.59 to 11.05 mm insulation height.
2024-02-12 Changes to ks7roh files.
2024-02-22 Created working directory for Arduino version
2024-02-22 Added pictures directory
2024-02-25 Add ks7roh code for the HR500 amp.
2024-02-25 Change to ks7roh README.md
2024-02-26 Added filter picture
2024-02-28 Added 2 pictures for readme
2024-03-04 Renamed Connector Lead.jpg to ConnectorLead.jpg
2024-03-05 Added source code and picture
2024-03-05 Renamed HL2_IO_Brd.ino to zl2te_arduino.ino
2024-03-05 Update hl2ioboard.h, cleared old test code
2024-03-05 Added ArduinoIDEcompile.png
2024-03-06 Update README.md - fixed typo
2024-03-14 Changed IcomAh4 START line to J4 pin 7
2024-03-14 remove clash on IcomAh4GPIO22_Out6 & Update README.md
2024-05-23 Update README.md for REG_RF_INPUTS
2024-05-28 feature - IOBOard to SPE Expert initial commit
2025-01-21 Add cleaned g4brk_k3band example
2025-05-11 Changed icom_ah4.c to fix a bug in the bad tune notification and add documentation. Slight change to frequency_code.c. Add directory w5eim.
2025-05-14 I put back the old code in icom_ah4.c because it was working fine. The new code to fix the "bug" works but has slightly less noise immunity.
2025-06-14 Added new code from W5EIM. Removed directory w5eim and added directory yeasu_bcd.
